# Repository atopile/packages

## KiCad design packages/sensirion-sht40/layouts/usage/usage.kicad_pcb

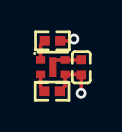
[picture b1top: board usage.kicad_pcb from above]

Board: 2 copper layers, 4 parts (0 on the bottom side), 4 nets.

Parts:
C1: 1F; C0402
R1, R2: 10000Ω; R0402
U1: DFN-4_L1.5-W1.5-P0.8-TL-EP

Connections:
SCL: R1.1, U1.2
SDA: R2.1, U1.1
hv: C1.1, R1.2, R2.2, U1.3
lv: C1.2, U1.4, U1.5

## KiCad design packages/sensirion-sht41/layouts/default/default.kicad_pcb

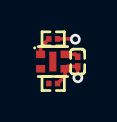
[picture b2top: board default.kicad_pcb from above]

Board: 2 copper layers, 4 parts (0 on the bottom side), 4 nets.

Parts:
C1: 1F; C0201
R1, R2: 10000Ω; R0201
U1: DFN-4_L1.5-W1.5-P0.80-TL-EP

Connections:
SCL: R1.2, U1.2
SDA: R2.2, U1.1
hv: C1.1, R1.1, R2.1, U1.3
lv: C1.2, U1.4
